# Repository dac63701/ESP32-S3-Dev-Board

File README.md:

# ESP32-S3-Dev-Board
A ESP32-S3 Dev Board with usb switch between an onboard UART bridge and the UART bridge included on the chip.

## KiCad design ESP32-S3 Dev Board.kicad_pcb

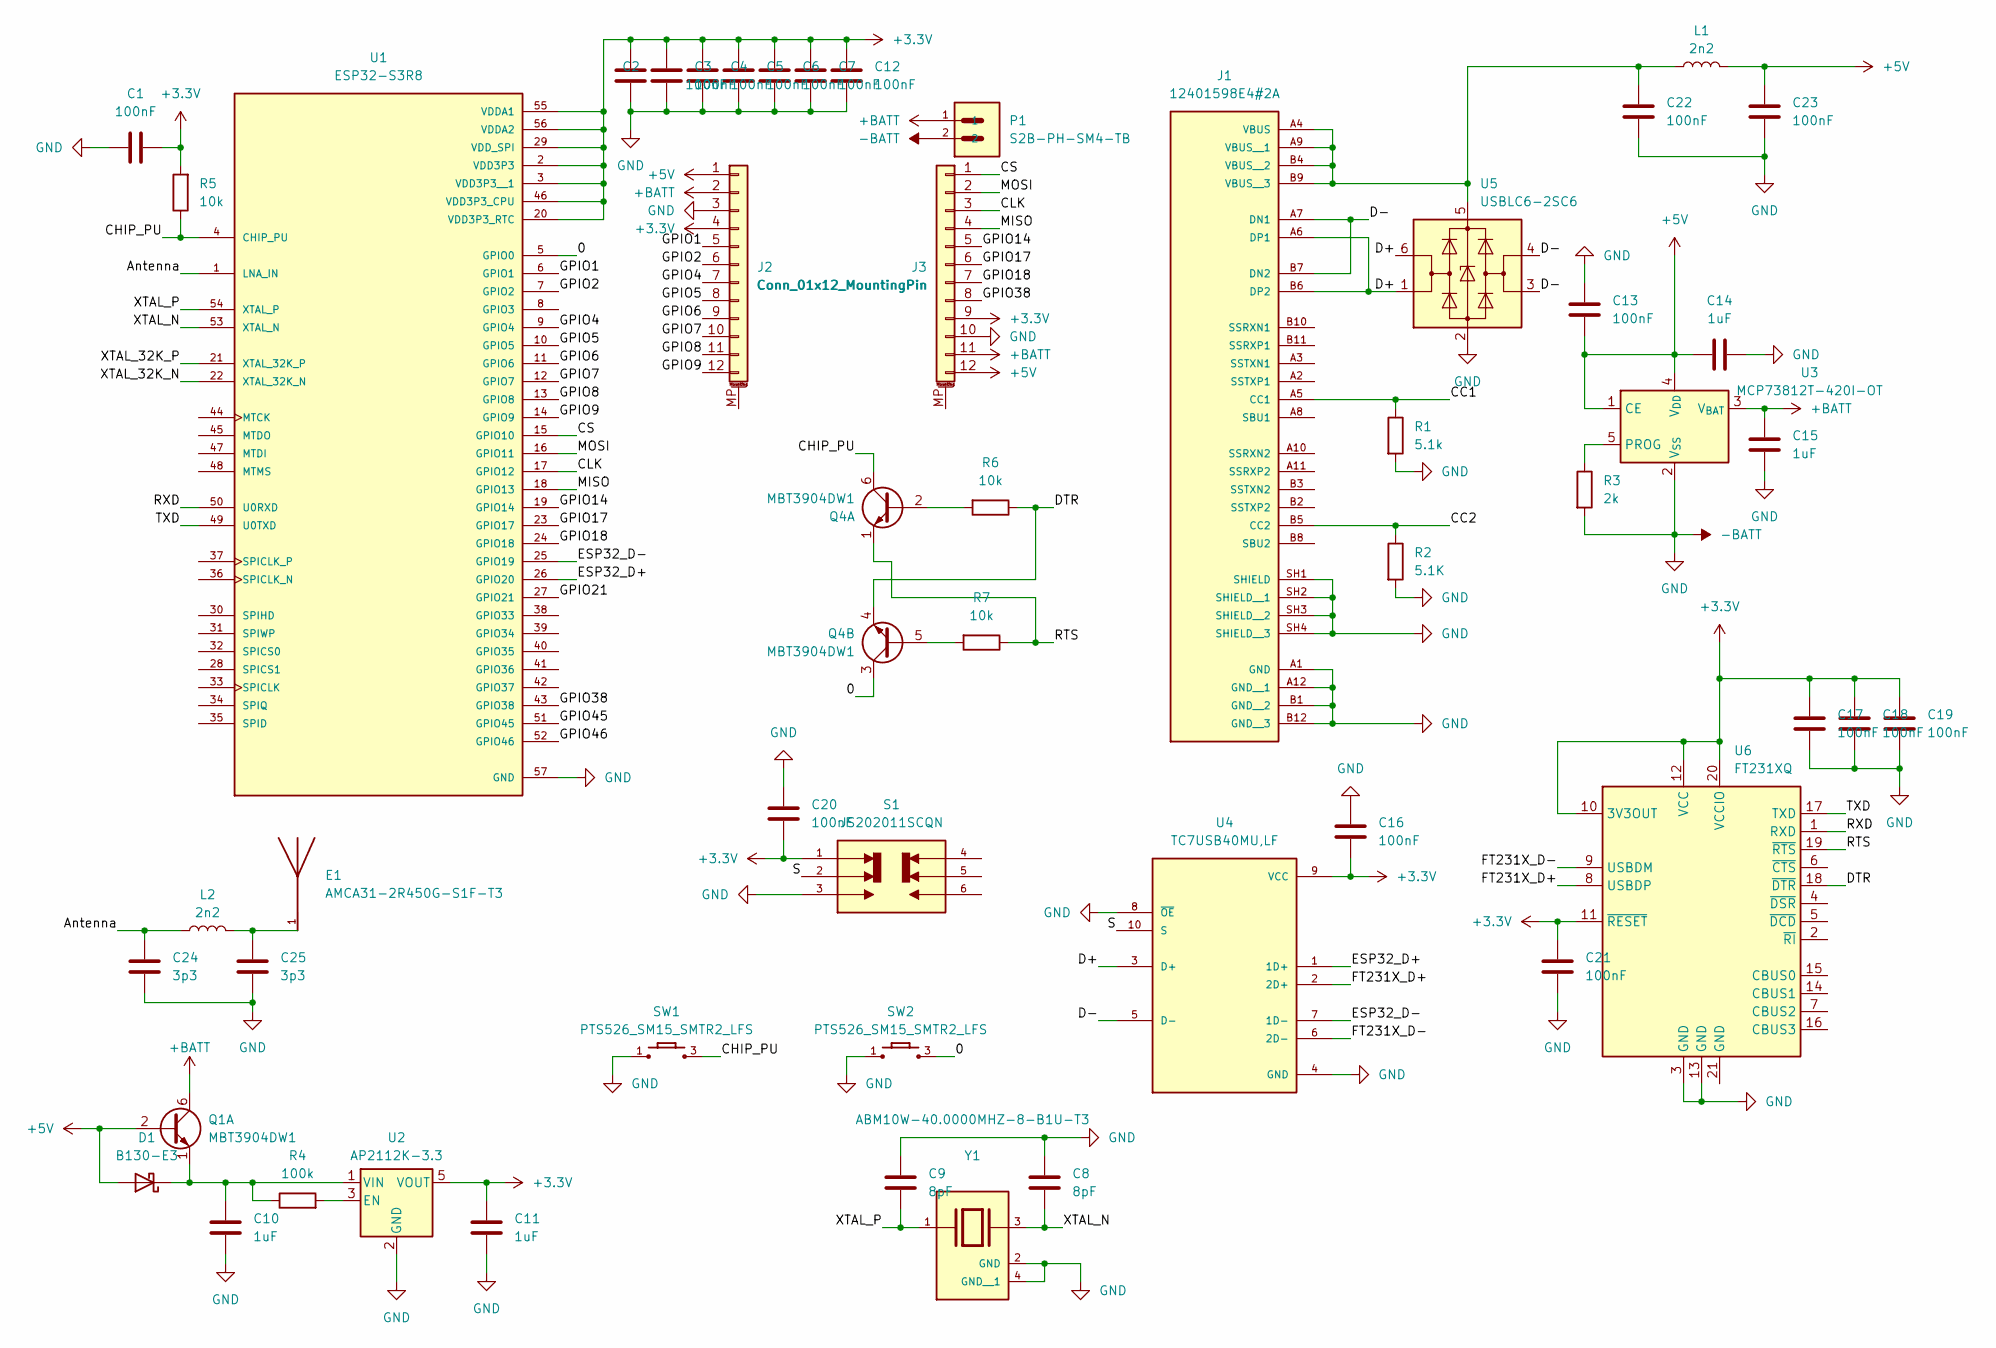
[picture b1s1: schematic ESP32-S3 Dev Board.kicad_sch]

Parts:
C1, C2, C3, C4, C5, C6, C7, C12, C13, C16, C17, C18, C19, C20, C21, C22, C23: 100nF; CAPC1005X55N
C8, C9: 8pF; CAPC1608X90
C10, C11, C14, C15: 1uF; CAPC1005X55N
C24, C25: 3p3; CAPC1005X55N
D1: B130-E3; D_SMA
E1: AMCA31-2R450G-S1F-T3; XDCR_AMCA31-2R450G-S1F-T3; PARTREV 03-21-19
J1: 12401598E4#2A; AMPHENOL_12401598E4#2A; PARTREV 4
J2, J3: Conn_01x12_MountingPin; PinHeader_1x12_P2.54mm_Vertical
L1, L2: 2n2; INDC1006X60N
P1: S2B-PH-SM4-TB; JST_S2B-PH-SM4-TB
Q1, Q4: MBT3904DW1; SOT-363_SC-70-6
R1: 5.1k; RESC1005X40N
R2: 5.1K; RESC1005X40N
R3: 2k; R0402
R4: 100k; RESC1005X35N
R5, R6, R7: 10k; R0402
S1: JS202011SCQN; SW_JS202011SCQN; PARTREV 26 May 22
SW1, SW2: PTS526_SM15_SMTR2_LFS; PTS526SM15SMTR2LFS; MOUSER_PART_NUMBER 611-PTS526SM15SMTR2L
U1: ESP32-S3R8; QFN40P700X700X90-57N
U2: AP2112K-3.3; SOT-23-5
U3: MCP73812T-420I-OT; SOT-23-5
U4: TC7USB40MU,LF; IC_TC7USB40MU,LF; PARTREV 1.0
U5: USBLC6-2SC6; SOT-23-6
U6: FT231XQ; QFN-20-1EP_4x4mm_P0.5mm_EP2.5x2.5mm
Y1: ABM10W-40.0000MHZ-8-B1U-T3; XTAL_ABM10W-40.0000MHZ-7-B1U-T3; PARTREV 10.06.2020

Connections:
+3.3V: C1.1, C2.2, C3.2, C4.2, C5.2, C6.2, C7.2, C11.2, C12.2, C16.2, C17.2, C18.2, C19.2, C20.1, C21.2, J2.4, J3.9, R5.2, S1.1, U1.2 (VDD3P3), U1.3 (VDD3P3__1), U1.20 (VDD3P3_RTC), U1.29 (VDD_SPI), U1.46 (VDD3P3_CPU), U1.55 (VDDA1), U1.56 (VDDA2), U2.5 (VOUT), U4.9 (VCC), U6.10 (3V3OUT), U6.11 (~RESET), U6.12 (VCC), U6.20 (VCCIO)
+5V: C13.2, C14.1, C23.1, D1.2 (A), J2.1, J3.12, L1.2, Q1.2 (B1), U3.1 (CE), U3.4 (V_{DD})
+BATT: C15.2, J2.2, J3.11, P1.1, Q1.6 (C1), U3.3 (V_{BAT})
-BATT: C1.2, C2.1, C3.1, C4.1, C5.1, C6.1, C7.1, C8.1, C9.1, C10.1, C11.1, C12.1, C13.1, C14.2, C15.1, C16.1, C17.1, C18.1, C19.1, C20.2, C21.1, C22.2, C23.2, C24.1, C25.1, J1.A1 (GND), J1.A12 (GND__1), J1.B1 (GND__2), J1.B12 (GND__3), J1.SH1 (SHIELD), J1.SH2 (SHIELD__1), J1.SH3 (SHIELD__2), J1.SH4 (SHIELD__3), J2.3, J3.10, P1.2, R1.2, R2.2, R3.2, S1.3, SW1.1, SW2.1, U1.57 (GND), U2.2 (GND), U3.2 (V_{SS}), U4.4 (GND), U4.8 (~OE), U5.2 (GND), U6.3 (GND), U6.13 (GND), Y1.2 (GND), Y1.4 (GND__1)
/0: Q4.3 (C2), SW2.3, U1.5 (GPIO0)
/Antenna: C24.2, L2.1, U1.1 (LNA_IN)
/CC1: J1.A5 (CC1), R1.1
/CC2: J1.B5 (CC2), R2.1
/CHIP_PU: Q4.6 (C1), R5.1, SW1.3, U1.4 (CHIP_PU)
/CLK: J3.3, U1.17 (GPIO12)
/CS: J3.1, U1.15 (GPIO10)
/D+: J1.A6 (DP1), J1.B6 (DP2), U4.3 (D+), U5.1 (I/O1), U5.6 (I/O1)
/D-: J1.A7 (DN1), J1.B7 (DN2), U4.5 (D-), U5.3 (I/O2), U5.4 (I/O2)
/DTR: Q4.4 (E2), R6.1, U6.18 (~DTR)
/ESP32_D+: U1.26 (GPIO20), U4.1 (1D+)
/ESP32_D-: U1.25 (GPIO19), U4.7 (1D-)
/FT231X_D+: U4.2 (2D+), U6.8 (USBDP)
/FT231X_D-: U4.6 (2D-), U6.9 (USBDM)
/GPIO1: J2.5, U1.6 (GPIO1)
/GPIO2: J2.6, U1.7 (GPIO2)
/GPIO4: J2.7, U1.9 (GPIO4)
/GPIO5: J2.8, U1.10 (GPIO5)
/GPIO6: J2.9, U1.11 (GPIO6)
/GPIO7: J2.10, U1.12 (GPIO7)
/GPIO8: J2.11, U1.13 (GPIO8)
/GPIO9: J2.12, U1.14 (GPIO9)
/GPIO14: J3.5, U1.19 (GPIO14)
/GPIO17: J3.6, U1.23 (GPIO17)
/GPIO18: J3.7, U1.24 (GPIO18)
/GPIO21: U1.27 (GPIO21)
/GPIO38: J3.8, U1.43 (GPIO38)
/GPIO45: U1.51 (GPIO45)
/GPIO46: U1.52 (GPIO46)
/MISO: J3.4, U1.18 (GPIO13)
/MOSI: J3.2, U1.16 (GPIO11)
/RTS: Q4.1 (E1), R7.1, U6.19 (~RTS)
/RXD: U1.50 (U0RXD), U6.1 (RXD)
/S: S1.2, U4.10 (S)
/TXD: U1.49 (U0TXD), U6.17 (TXD)
/XTAL_32K_N: U1.22 (XTAL_32K_N)
/XTAL_32K_P: U1.21 (XTAL_32K_P)
/XTAL_N: C8.2, U1.53 (XTAL_N), Y1.3
/XTAL_P: C9.2, U1.54 (XTAL_P), Y1.1
unnamed: C25.2, E1.1, L2.2
unnamed: C10.2, D1.1 (K), Q1.1 (E1), R4.1, U2.1 (VIN)
unnamed: C22.1, J1.A4 (VBUS), J1.A9 (VBUS__1), J1.B4 (VBUS__2), J1.B9 (VBUS__3), L1.1, U5.5 (VBUS)
unnamed: Q4.2 (B1), R6.2
unnamed: Q4.5 (B2), R7.2
unnamed: R4.2, U2.3 (EN)
unnamed: R3.1, U3.5 (PROG)

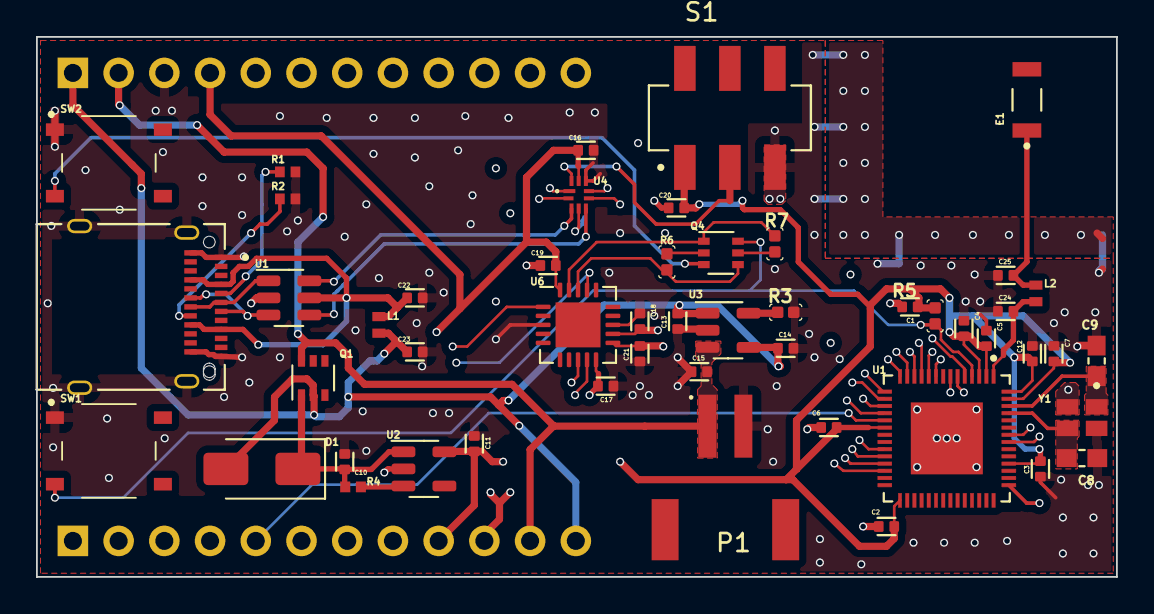
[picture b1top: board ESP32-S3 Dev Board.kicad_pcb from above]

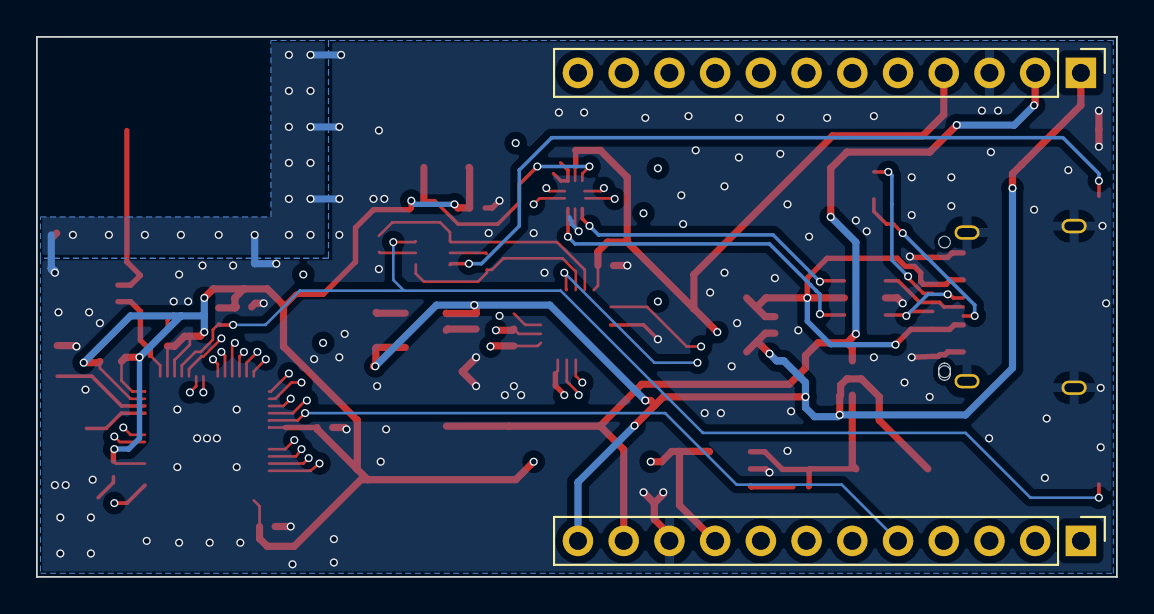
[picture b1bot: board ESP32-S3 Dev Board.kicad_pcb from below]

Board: 4 copper layers, 60.0 x 30.0 mm, 52 parts (2 on the bottom side), 45 nets.
